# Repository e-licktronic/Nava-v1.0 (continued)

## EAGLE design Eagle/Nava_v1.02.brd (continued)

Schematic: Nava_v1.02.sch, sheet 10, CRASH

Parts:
C50: 100p; C050-025X075
C60, C86, C87, C127, C132: 10/16; E2-5
C126, C137: 0.001; C050-025X075
C131: 470p; C025_RE
C136: 0.0012; C050-025X075
C138: 0.0027; C050-025X075
C139: 390p; C025_RE
IC51, IC52, IC65: M5218; SIL8
IC58: 4520N; DIL16
IC59: 4011UB; DIL14
IC60: 4013N; DIL14
IC61: 4040N; DIL16
IC62: 27C256P; DIL28-6
IC63: 74HC174; DIL16
J3: 22-27-2041-04; 6410-04
Q70: 2SA798; SIP-5
Q71, Q75, Q76: 2SC2603; TO92-ECB
R189: 100K; 0207/7
R425: 47K; 0207/7
R426: 4.7K; 0207/7
R427, R430: 2.2K; 0207/7
R428: 220R; 0207/7
R429: 100R; 0207/7
R431: 22R; 0207/7
R432: 270K; 0207/7
R442, R458, R460: 10K; 0207/7
R443: 6.8K; 0207/7
R445: 22K; 0207/7
R456, R457, R459, R461: 5.6K; 0207/7
RA10A, RA11A: 5K; 0207/7
RA10B, RA11B: 10K; 0207/7
RA10C, RA11C: 20K; 0207/7
RA10D, RA11D: 40K; 0207/7
RA10E, RA11E: 80K; 0207/7
RA10F, RA11F: 160K; 0207/7
VR24: 50KB; EVUF
VR25: 10KB; EVUF

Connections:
+5V: C87.+, IC52.5 (+IN), IC59.14 (VDD), IC60.14 (VDD), IC61.16 (VDD), IC62.1 (VPP), IC62.28 (VCC), IC63.1 (RES), IC63.16 (VDD), R428.2, R429.2; also elsewhere on the board
+VRI: C60.+, IC65.8 (V+), Q75.C, Q76.C; also elsewhere on the board
-VRI: C86.-, IC65.4 (V-), R458.2, R460.2; also elsewhere on the board
ACCENT_CRASH: R426.1; also elsewhere on the board
CRASH_OUT: IC65.1 (OUT), J3.2, VR24.2 (S), VR24.3 (E)
GND: C60.-, C86.+, C87.-, C137.1, C139.- (2), IC51.5 (+IN), IC58.1 (CLK), IC59.7 (VSS), IC60.6 (S), IC60.7 (VSS), IC60.8 (S), IC61.8 (VSS), IC62.14 (GND), IC63.8 (VSS), IC65.3 (+IN), R189.2, R431.1, VR24.M1, VR25.M1; also elsewhere on the board
HT_OUT2: IC59.6 (I1), IC59.10 (O), IC60.11 (CLK), VR25.1 (A), VR25.2 (S)
unnamed: Q70.3 (E), R430.1
unnamed: R443.1, VR25.3 (E)
unnamed: IC59.8 (I0), IC59.9 (I1), R442.2
unnamed: C131.+ (1), R442.1, R443.2
unnamed: IC59.5 (I0), IC59.11 (O), R427.1
unnamed: C131.- (2), IC59.4 (O), IC60.3 (CLK)
unnamed: IC60.9 (D), IC60.12 (!Q)
unnamed: IC60.2 (!Q), IC60.5 (D), IC62.22 (!OE)
unnamed: IC59.1 (I0), IC60.13 (Q)
unnamed: IC59.3 (O), IC63.9 (CLK)
unnamed: IC59.2 (I1), IC60.1 (Q), IC61.10 (P1)
unnamed: IC62.19 (D7), IC63.3 (D0)
unnamed: IC62.18 (D6), IC63.4 (D1)
unnamed: IC62.17 (D5), IC63.6 (D2)
unnamed: IC62.16 (D4), IC63.11 (D3)
unnamed: IC62.15 (D3), IC63.13 (D4)
unnamed: IC62.13 (D2), IC63.14 (D5)
unnamed: C127.+, RA10A.2, RA10B.2, RA10C.2, RA10D.2, RA10E.2, RA10F.2
unnamed: R432.1, RA11A.2, RA11B.2, RA11C.2, RA11D.2, RA11E.2, RA11F.2
unnamed: C126.1, IC52.6 (-IN), Q70.2 (C1), R432.2
unnamed: C126.2, IC52.7 (OUT), R430.2
unnamed: Q70.5 (B2), R429.1
unnamed: C127.-, Q71.C, R431.2
unnamed: Q70.1 (B1), R426.2, R427.2, R428.1
unnamed: Q70.4 (C2), Q71.B
unnamed: C138.2, R459.1, R461.2
unnamed: C136.2, R456.1, R457.2
unnamed: C137.2, Q75.B, R457.1
unnamed: C139.+ (1), Q76.B, R461.1
unnamed: IC51.6 (-IN), Q71.E, R425.2
unnamed: IC51.7 (OUT), R425.1, R456.2
unnamed: C136.1, Q75.E, R458.1, R459.2
unnamed: C132.-, C138.1, Q76.E, R460.1
unnamed: IC65.2 (-IN), R445.1, VR24.1 (A)
unnamed: C132.+, R445.2
unnamed: IC58.2 (EN), IC61.1 (Q12), IC62.23 (A11), RA11D.1
unnamed: IC61.2 (Q6), IC62.5 (A5)
unnamed: IC61.3 (Q5), IC62.6 (A4)
unnamed: IC61.4 (Q7), IC62.4 (A6)
unnamed: IC61.5 (Q4), IC62.7 (A3)
unnamed: IC61.6 (Q3), IC62.8 (A2)
unnamed: IC61.7 (Q2), IC62.9 (A1)
unnamed: IC61.9 (Q1), IC62.10 (A0)
unnamed: IC61.12 (Q9), IC62.25 (A8)
unnamed: IC61.13 (Q8), IC62.3 (A7)
unnamed: IC61.14 (Q10), IC62.24 (A9), RA11F.1
unnamed: IC61.15 (Q11), IC62.21 (A10), RA11E.1
unnamed: IC58.3 (Q0), IC62.2 (A12), RA11C.1
unnamed: IC58.4 (Q1), IC62.26 (A13), RA11B.1
unnamed: IC58.5 (Q2), IC62.27 (A14), RA11A.1
unnamed: IC58.6 (Q3), IC59.12 (I0), IC59.13 (I1), IC62.20 (!CE)
unnamed: IC63.2 (Q0), RA10A.1
unnamed: IC63.5 (Q1), RA10B.1
unnamed: IC63.7 (Q2), RA10C.1
unnamed: IC63.10 (Q3), RA10D.1
unnamed: IC63.12 (Q4), RA10E.1
unnamed: C50.2, IC58.7 (RES), IC60.4 (R), IC60.10 (R), IC61.11 (RES), R189.1
unnamed: IC63.15 (Q5), RA10F.1
TRIG_CRASH: C50.1; also elsewhere on the board

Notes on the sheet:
Crash

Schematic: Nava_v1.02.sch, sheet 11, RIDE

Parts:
C123, C124, C128, C129, C133: 10/16; E2-5
C125, C145: 0.001; C050-025X075
C130: 470p; C025_RE
C140: 100p; C050-025X075
C144: 0.0012; C050-025X075
C146: 0.0027; C050-025X075
C147: 390p; C025_RE
IC51, IC52, IC64: M5218; SIL8
IC53: 74HC174; DIL16
IC54: 27C256P; DIL28-6
IC55: 4040N; DIL16
IC56: 4013N; DIL14
IC57: 4011UB; DIL14
IC58: 4520N; DIL16
J3: 22-27-2041-04; 6410-04
Q68: 2SA798; SIP-5
Q69, Q77, Q78: 2SC2603; TO92-ECB
R188: 100K; 0207/7
R424: 47K; 0207/7
R433: 220R; 0207/7
R434: 100R; 0207/7
R435: 4.7K; 0207/7
R436, R437: 2.2K; 0207/7
R438: 22R; 0207/7
R439: 470K; 0207/7
R440, R464, R466: 10K; 0207/7
R441: 6.8K; 0207/7
R446: 22K; 0207/7
R462, R463, R465, R467: 5.6K; 0207/7
RA12A, RA13A: 5K; 0207/7
RA12B, RA13B: 10K; 0207/7
RA12C, RA13C: 20K; 0207/7
RA12D, RA13D: 40K; 0207/7
RA12E, RA13E: 80K; 0207/7
RA12F, RA13F: 160K; 0207/7
RP7, RP8: 0; 0207/7
VR26: 50KB; EVUF
VR27: 10KB; EVUF

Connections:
+5V: C129.+, IC52.3 (+IN), IC53.1 (RES), IC53.16 (VDD), IC54.1 (VPP), IC54.28 (VCC), IC55.16 (VDD), IC56.14 (VDD), IC57.14 (VDD), IC58.16 (VDD), R433.2, R434.2; also elsewhere on the board
+15V: RP7.1; also elsewhere on the board
+VRI: C123.+, IC51.8 (V+), IC52.8 (V+), IC64.8 (V+), Q77.C, Q78.C, RP7.2; also elsewhere on the board
-15V: RP8.2; also elsewhere on the board
-VRI: C124.-, IC51.4 (V-), IC52.4 (V-), IC64.4 (V-), R464.2, R466.2, RP8.1; also elsewhere on the board
ACCENT_RIDE: R435.1; also elsewhere on the board
GND: C123.-, C124.+, C129.-, C145.1, C147.- (2), IC51.3 (+IN), IC53.8 (VSS), IC54.14 (GND), IC55.8 (VSS), IC56.6 (S), IC56.7 (VSS), IC56.8 (S), IC57.7 (VSS), IC58.8 (VSS), IC58.9 (CLK), IC64.3 (+IN), IC64.5 (+IN), R188.2, R438.1, VR26.M1, VR27.M1; also elsewhere on the board
HT_OUT1: IC56.11 (CLK), IC57.4 (O), IC57.8 (I0), VR27.1 (A), VR27.2 (S)
unnamed: Q68.3 (E), R436.1
unnamed: IC56.1 (Q), IC57.13 (I1), IC58.10 (EN)
unnamed: IC53.3 (D0), IC54.19 (D7)
unnamed: IC53.4 (D1), IC54.18 (D6)
unnamed: IC53.6 (D2), IC54.17 (D5)
unnamed: IC53.11 (D3), IC54.16 (D4)
unnamed: IC53.13 (D4), IC54.15 (D3)
unnamed: IC53.14 (D5), IC54.13 (D2)
unnamed: IC54.24 (A9), IC55.2 (Q6), RA13F.1
unnamed: IC54.25 (A8), IC55.3 (Q5)
unnamed: IC54.21 (A10), IC55.4 (Q7), RA13E.1
unnamed: IC54.3 (A7), IC55.5 (Q4)
unnamed: IC54.4 (A6), IC55.6 (Q3)
unnamed: IC54.5 (A5), IC55.7 (Q2)
unnamed: IC54.6 (A4), IC55.9 (Q1)
unnamed: IC54.2 (A12), IC55.12 (Q9), RA13C.1
unnamed: IC54.23 (A11), IC55.13 (Q8), RA13D.1
unnamed: IC54.26 (A13), IC55.14 (Q10), RA13B.1
unnamed: IC54.27 (A14), IC55.15 (Q11), RA13A.1
unnamed: IC54.10 (A0), IC58.11 (Q0)
unnamed: IC54.9 (A1), IC58.12 (Q1)
unnamed: IC57.5 (I0), IC57.6 (I1), R440.2
unnamed: IC54.8 (A2), IC58.13 (Q2)
unnamed: C130.+ (1), R440.1, R441.2
unnamed: IC57.3 (O), IC57.9 (I1), R437.1
unnamed: C130.- (2), IC56.3 (CLK), IC57.10 (O)
unnamed: IC54.20 (!CE), IC55.1 (Q12), IC57.1 (I0), IC57.2 (I1)
unnamed: IC53.2 (Q0), RA12A.1
unnamed: C146.2, R465.1, R467.2
unnamed: IC56.9 (D), IC56.12 (!Q)
unnamed: IC54.22 (!OE), IC56.2 (!Q), IC56.5 (D)
unnamed: IC56.13 (Q), IC57.12 (I0)
unnamed: IC53.5 (Q1), RA12B.1
unnamed: IC53.7 (Q2), RA12C.1
unnamed: IC53.9 (CLK), IC57.11 (O)
unnamed: IC53.10 (Q3), RA12D.1
unnamed: IC53.12 (Q4), RA12E.1
unnamed: IC53.15 (Q5), RA12F.1
unnamed: C128.+, RA12A.2, RA12B.2, RA12C.2, RA12D.2, RA12E.2, RA12F.2
unnamed: R439.1, RA13A.2, RA13B.2, RA13C.2, RA13D.2, RA13E.2, RA13F.2
unnamed: C125.1, IC52.2 (-IN), Q68.2 (C1), R439.2
unnamed: C125.2, IC52.1 (OUT), R436.2
unnamed: Q68.5 (B2), R434.1
unnamed: Q68.4 (C2), Q69.B
unnamed: C128.-, Q69.C, R438.2
unnamed: Q68.1 (B1), R433.1, R435.2, R437.2
unnamed: C144.2, R462.1, R463.2
unnamed: C145.2, Q77.B, R463.1
unnamed: C147.+ (1), Q78.B, R467.1
unnamed: IC51.2 (-IN), Q69.E, R424.2
unnamed: IC51.1 (OUT), R424.1, R462.2
unnamed: C144.1, Q77.E, R464.1, R465.2
unnamed: C133.+, R446.2
unnamed: C133.-, C146.1, Q78.E, R466.1
unnamed: IC64.2 (-IN), R446.1, VR26.1 (A)
unnamed: IC54.7 (A3), IC55.10 (P1), IC58.14 (Q3)
unnamed: C140.2, IC55.11 (RES), IC56.4 (R), IC56.10 (R), IC58.15 (RES), R188.1
unnamed: IC64.6 (-IN), IC64.7 (OUT)
unnamed: R441.1, VR27.3 (E)
RIDE_OUT: IC64.1 (OUT), J3.1, VR26.2 (S), VR26.3 (E)
TRIG_RIDE: C140.1; also elsewhere on the board

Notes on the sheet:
Ride

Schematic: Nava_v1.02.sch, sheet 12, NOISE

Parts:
C46: 4.7/50; E2-5
C47: 100p; C050-025X075
C48: 0.1; C050-024X044
C51, C52, C54, C161: 0.0047; C050-025X075
C53: 0.047; C050-025X075
D1, D2, D3, D26, D44, D45, D48, D49: 1N4148"; DO35-7C
IC27: M5218; SIL8
IC31: 4070N; DIL14
IC32, IC33: 4006N; DIL14
Q33, Q34: 2SC2603; TO92-ECB
R182, R183, R184, R191, R197: 10K; 0207/7
R185: 33K; 0207/7
R186, R194, R198, R200: 100K; 0207/7
R187: 47K; 0207/7
R190, R193, R196: 22K; 0207/7
R192: 220K; 0207/7
R195: 1K; 0207/7
R199: 47R; 0207/7
RP11, RP12: 0; 0207/7

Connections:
+15V: RP11.2; also elsewhere on the board
+VMT: C46.+, C48.1, IC27.8 (V+), IC31.2 (I1), IC31.14 (VDD), IC32.14 (VDD), IC33.14 (VDD), RP11.1; also elsewhere on the board
-15V: RP12.2; also elsewhere on the board
-VMT: IC27.4 (V-), RP12.1; also elsewhere on the board
GND: C48.2, C54.2, C161.2, D49.A, IC27.3 (+IN), IC31.6 (I1), IC31.7 (VSS), IC31.12 (I0), IC32.7 (VSS), IC33.7 (VSS), Q34.E, R182.1, R192.1, R197.2, R199.1; also elsewhere on the board
unnamed: C51.2, C161.1, R190.1
unnamed: C51.1, C52.2, R191.1
unnamed: C52.1, IC27.5 (+IN), R192.2
unnamed: C53.2, IC27.6 (-IN), IC27.7 (OUT), R191.2, R194.2
unnamed: C53.1, R195.1
unnamed: Q33.C, R195.2, R199.2
unnamed: IC27.2 (-IN), Q33.E, R193.2, R194.1
unnamed: Q33.B, R200.2
unnamed: Q34.B, R196.2, R197.1
unnamed: Q34.C, R198.2, R200.1
unnamed: IC32.4 (D2), IC32.13 (D1+4)
unnamed: D1.C, D2.C, D3.C, R196.1
unnamed: C54.1, D26.C, D44.C, D45.C, R198.1
unnamed: C46.-, D49.C, R182.2, R183.2
unnamed: IC31.13 (I1), R183.1, R186.2
unnamed: D48.A, IC31.11 (O), R186.1
unnamed: IC31.10 (O), R187.1
unnamed: IC33.4 (D2), IC33.13 (D1+4)
unnamed: IC31.9 (I1), IC32.6 (D4), IC32.10 (D3+4)
unnamed: IC32.5 (D3), IC32.12 (D2+5)
unnamed: D48.C, IC32.1 (D1), R187.2
unnamed: IC31.8 (I0), IC33.6 (D4), IC33.10 (D3+4)
unnamed: IC33.5 (D3), IC33.12 (D2+5)
unnamed: IC32.9 (D4+5), IC33.1 (D1)
unnamed: IC31.5 (I0), R185.2
unnamed: C47.1, R184.2, R185.1
unnamed: C47.2, IC31.1 (I0), IC31.4 (O)
unnamed: IC31.3 (O), IC32.3 (CLK), IC33.3 (CLK), R184.1
NOISE: IC33.9 (D4+5), R190.2; also elsewhere on the board
TOM_NOISE: IC27.1 (OUT), R193.1; also elsewhere on the board
TO_NOISE_HT: D26.A; also elsewhere on the board
TO_NOISE_LT: D45.A; also elsewhere on the board
TO_NOISE_MT: D44.A; also elsewhere on the board
TRIG_HT: D3.A; also elsewhere on the board
TRIG_LT: D1.A; also elsewhere on the board
TRIG_MT: D2.A; also elsewhere on the board

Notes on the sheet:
Noise

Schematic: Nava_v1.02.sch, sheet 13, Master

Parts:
C142, C152, C155: 10/16; E2-5
C143: 47/35; E2,5-6
C153, C154: 1/50; E2-5
D193, D194, D195: 1N4148"; DO35-7C
IC66: M5218; SIL8
J6: 22-27-2061-06; 6410-06
Q79: 2SA1115; TO92-ECB-PNP
Q82, Q83: 2SC2878; TO92-ECB
R468: 10K; 0207/7
R469, R470: 22K; 0207/7
R471: 4.7K; 0207/7
R472: 470K; 0207/7
R473, R474: 1K; 0207/7
RP19, RP20: 0; 0207/7
VR28: 50KB; PTV112-4

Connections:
+15V: RP19.1; also elsewhere on the board
+VMS: C143.+, D193.A, IC66.8 (V+), R468.1, RP19.2
-15V: RP20.1; also elsewhere on the board
-VMS: IC66.4 (V-), R471.2, R472.2, RP20.2
GND: C142.-, IC66.3 (+IN), IC66.5 (+IN), J6.2, J6.4, Q82.E, Q83.E; also elsewhere on the board
unnamed: D195.A, R471.1
unnamed: C143.-, D194.A, D195.C, R472.1
unnamed: IC66.7 (OUT), R474.1, VR28.1
unnamed: IC66.1 (OUT), R473.1, VR28.1' (1)
unnamed: D194.C, Q79.C, R469.1, R470.1
unnamed: C142.+, D193.C, Q79.E
unnamed: Q79.B, R468.2
unnamed: C154.-, IC66.2 (-IN), VR28.2' (2)
unnamed: C153.-, IC66.6 (-IN), VR28.2
unnamed: C155.-, R474.2
unnamed: C152.-, R473.2
unnamed: Q82.B, R469.2
unnamed: Q83.B, R470.2
unnamed: C153.+, J6.3
unnamed: C155.+, J6.5, Q83.C
unnamed: C152.+, J6.6, Q82.C
unnamed: C154.+, J6.1

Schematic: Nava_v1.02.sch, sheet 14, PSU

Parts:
C49, C88, C92, C93: 0.1; C050-024X044
C90, C91: 2200/35; E7,5-16
C94: 220/35; E3,5-8
C114, C141: 100/35; E3,5-8
C162: 680/35; E5-13
D94, D95, D96, D97, D109, D110, D111: 1N4004; DO41-7
D101: 1N5819-B; DO41-7.6
J8: KK-156-5
J9: KK-156-2
J16: JACK-PLUG0; JACK_PSU_2.1MM
L1: 33u; BS11
R40: 0; 0207/7
REG1: 7815TV; TO220V
REG2: MC79M15BT; TO220V
REG3: LM2596T; T05D

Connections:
+5V: C94.+, J8.2, L1.1, REG3.4 (FB); also elsewhere on the board
GND: C49.1, C88.2, C90.-, C91.+, C92.2, C93.1, C94.-, C114.-, C141.+, C162.-, D94.C, D95.A, D101.A, J8.3, J8.4, J16.1, R40.1, R40.2, REG1.2 (GND), REG2.1 (GND), REG3.3 (GND), REG3.5 (!ON!/OFF); also elsewhere on the board
unnamed: C49.2, C91.-, D96.A, D110.A, REG2.2 (VI)
unnamed: C88.1, C90.+, D97.C, D109.C, REG1.1 (VI)
unnamed: C92.1, C114.+, D95.C, D97.A, J8.1, REG1.3 (VO)
unnamed: D109.A, D110.C, D111.A, J9.2
unnamed: C93.2, C141.-, D94.A, D96.C, J8.5, REG2.3 (VO)
unnamed: C162.+, D111.C, REG3.1 (VIN)
unnamed: D101.C, L1.2, REG3.2 (OUT)
unnamed: J9.1, J16.3

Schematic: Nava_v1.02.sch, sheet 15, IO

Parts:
4, 5: LSP10
BASSDRUM: JACK_TRSNRJ6HF; JACK_TRS
C500, C502, C503, C504, C505, C506, C507, C508, C509, C510, C511, C512: 0.01; C050-025X075
CRASH: JACK_TRSNRJ6HF; JACK_TRS
D98: 1N4148"; DO35-7C
DIN_SYNC: MAB5SH
HANDCLAP: JACK_TRSNRJ6HF; JACK_TRS
HIHAT: JACK_TRSNRJ6HF; JACK_TRS
HITOM: JACK_TRSNRJ6HF; JACK_TRS
IC4: 6N138"; DIL08
IN: MAB5SH
J10: 22-27-2081-08; 6410-08
J11, J12, J13: 22-27-2041-04; 6410-04
J14: 22-27-2061-06; 6410-06
LEFT: JACK_TRSNRJ6HF; JACK_TRS
LOWTOM: JACK_TRSNRJ6HF; JACK_TRS
MIDTOM: JACK_TRSNRJ6HF; JACK_TRS
OUT: MAB5SH
Q66: 2N3906; TO92-EBC-SMALL
R314: 5.6K; 0207/7
R315, R316, R317, R318, R319: 220; 0207/7
R326, R327, R530, R532: 2.2K; 0207/7
R328, R330: 100K; 0207/7
R365: 1.2K; 0207/7
R500, R503, R506, R509, R512, R515, R518, R521, R524, R527, R552: 1K; 0207/7
R501, R502, R504, R505, R510, R511, R516, R517, R519, R520, R525: 12K; 0207/7
R507, R514, R523, R528: 8.2K; 0207/7
R508, R513, R522, R529: 15K; 0207/7
R526, R531, R533: 10K; 0207/7
R550: 47K; 0207/7
R551: 22K; 0207/7
RIDE: JACK_TRSNRJ6HF; JACK_TRS
RIGHT/MONO: JACK_TRSNRJ6HF; JACK_TRS
RIMSHOT: JACK_TRSNRJ6HF; JACK_TRS
SNAREDRUM: JACK_TRSNRJ6HF; JACK_TRS
THRU: MAB5SH
TRIG1: JACK_TRSNRJ6HF; JACK_TRS

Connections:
+5V: IC4.8 (VCC), J10.8, Q66.E, R315.2, R318.2, R365.1; also elsewhere on the board
DIN_CLK_IO: J10.4, R327.1, R330.1
DIN_START_IO: J10.5, R326.2, R328.1
GND: BASSDRUM.R, BASSDRUM.S, C500.1, C502.1, C503.1, C504.1, C505.1, C506.1, C507.1, C508.1, C509.1, C510.1, C511.1, C512.1, CRASH.R, CRASH.S, DIN_SYNC.2, DIN_SYNC.PE, DIN_SYNC.PE@ (PE), HANDCLAP.R, HANDCLAP.S, HIHAT.R, HIHAT.S, HITOM.R, HITOM.S, IC4.5 (GND), IN.PE, IN.PE@ (PE), J10.1, J10.2, J14.2, J14.4, LEFT.R, LEFT.S, LOWTOM.R, LOWTOM.S, MIDTOM.R, MIDTOM.S, OUT.2, OUT.PE, OUT.PE@ (PE), R314.1, R328.2, R330.2, R531.1, R533.1, R551.2, RIDE.R, RIDE.S, RIGHT/MONO.R, RIGHT/MONO.S, RIMSHOT.R, RIMSHOT.S, SNAREDRUM.R, SNAREDRUM.S, THRU.2, THRU.PE, THRU.PE@ (PE), TRIG1.R, TRIG1.S; also elsewhere on the board
MIDI_IN_IO: IC4.6 (VO), J10.7, R316.2, R365.2
MIDI_OUT_IO: J10.6, R319.2
unnamed: R552.1, TRIG1.T
unnamed: 5.MP, DIN_SYNC.5
unnamed: 4.MP, DIN_SYNC.4
unnamed: BASSDRUM.TN, R501.2, R502.2
unnamed: BASSDRUM.T, C500.2, R500.1
unnamed: Q66.B, R550.2
unnamed: J11.1, R500.2
unnamed: C512.2, LEFT.TN, R532.1, R533.2, RIGHT/MONO.T, RIGHT/MONO.TN
unnamed: R504.2, R505.2, SNAREDRUM.TN
unnamed: C502.2, R503.1, SNAREDRUM.T
unnamed: J11.2, R503.2
unnamed: C511.2, LEFT.T, R530.1, R531.2
unnamed: LOWTOM.TN, R507.2, R508.2
unnamed: C503.2, LOWTOM.T, R506.1
unnamed: J11.3, R506.2
unnamed: J12.1, R518.2
unnamed: MIDTOM.TN, R510.2, R511.2
unnamed: C504.2, MIDTOM.T, R509.1
unnamed: J12.2, R509.2
unnamed: J12.3, R515.2
unnamed: HITOM.TN, R513.2, R514.2
unnamed: C505.2, HITOM.T, R512.1
unnamed: J14.1, R502.1, R505.1, R508.1, R511.1, R514.1, R517.1, R520.1, R523.1, R526.1, R529.1
unnamed: J12.4, R512.2
unnamed: R516.2, R517.2, RIMSHOT.TN
unnamed: C506.2, R515.1, RIMSHOT.T
unnamed: J13.1, R527.2
unnamed: J13.2, R524.2
unnamed: HANDCLAP.TN, R519.2, R520.2
unnamed: IN.4, R317.1
unnamed: D98.C, IC4.2 (A), R317.2
unnamed: D98.A, IC4.3 (C), IN.5
unnamed: R315.1, THRU.4
unnamed: R316.1, THRU.5
unnamed: IC4.7 (VB), R314.2
unnamed: OUT.4, R318.1
unnamed: OUT.5, R319.1
unnamed: DIN_SYNC.1, R326.1
unnamed: DIN_SYNC.3, R327.2
unnamed: C507.2, HANDCLAP.T, R518.1
unnamed: Q66.C, R551.1, R552.2
unnamed: J13.3, R521.2
unnamed: HIHAT.TN, R522.2, R523.2
unnamed: C508.2, HIHAT.T, R521.1
unnamed: J14.5, R530.2
unnamed: J14.6, R532.2
unnamed: CRASH.TN, R525.2, R526.2
unnamed: C509.2, CRASH.T, R524.1
unnamed: R528.2, R529.2, RIDE.TN
unnamed: C510.2, R527.1, RIDE.T
unnamed: J14.3, R501.1, R504.1, R507.1, R510.1, R513.1, R516.1, R519.1, R522.1, R525.1, R528.1
TRIG_1_IO: J10.3, R550.1

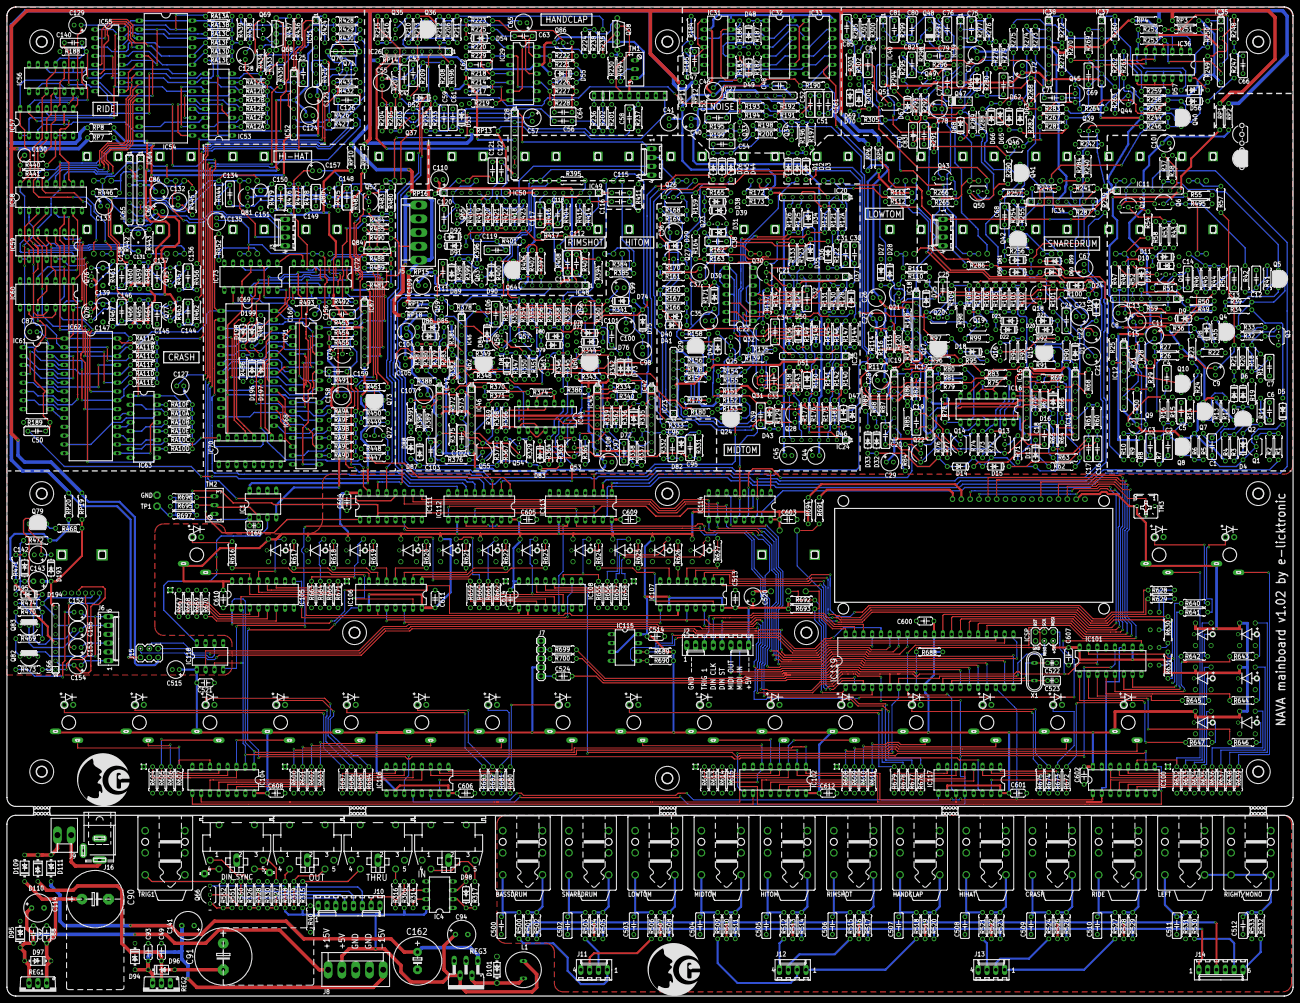
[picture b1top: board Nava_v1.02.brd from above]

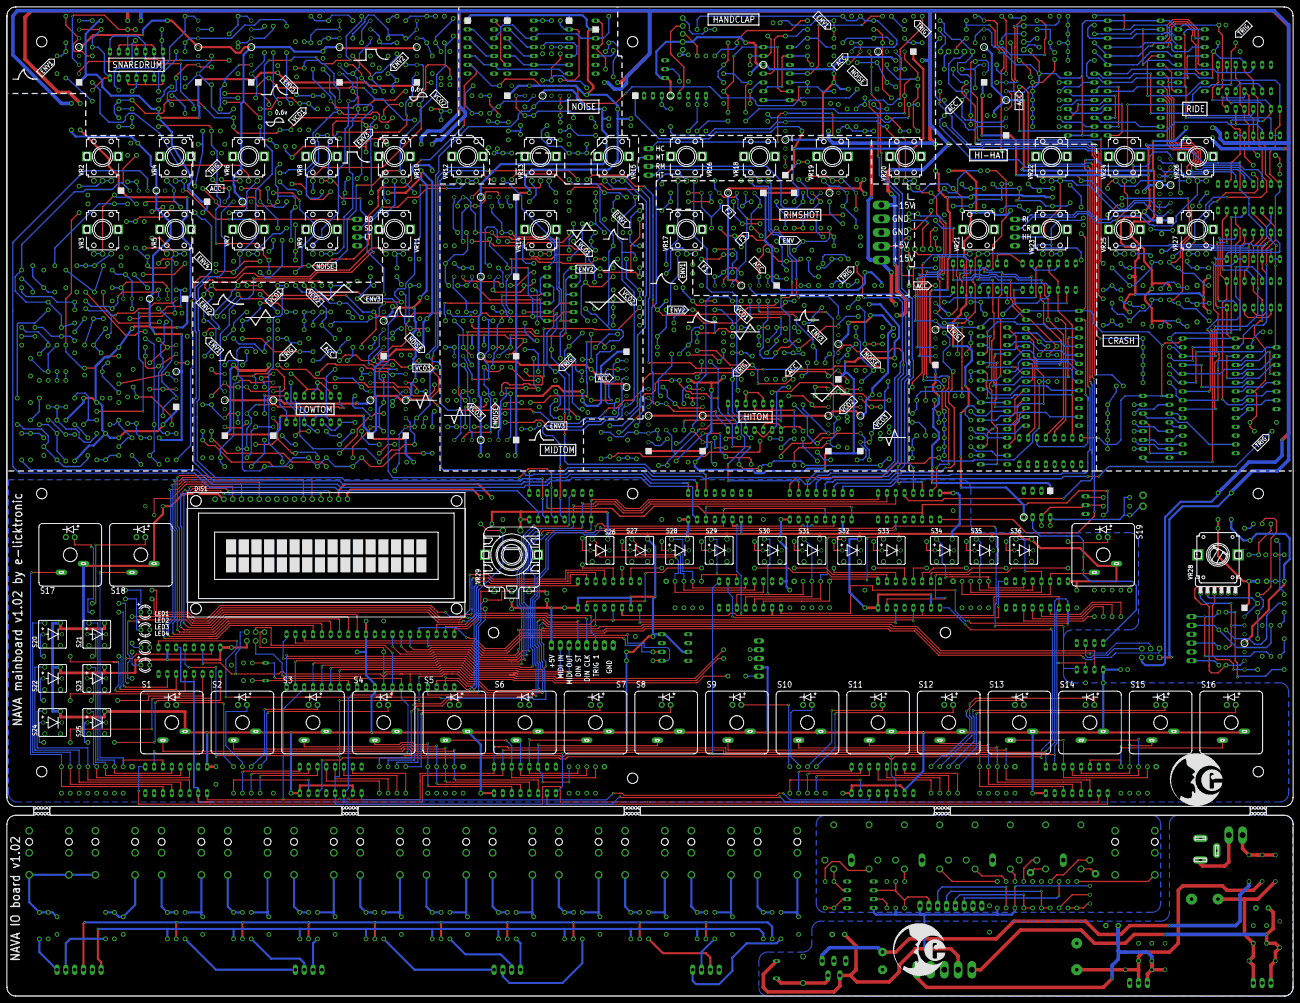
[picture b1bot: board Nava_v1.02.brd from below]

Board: 2 copper layers, 370.0 x 284.6 mm, 1261 parts (71 on the bottom side), 939 nets.

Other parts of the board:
U$1, U$13, U$14, U$15: LOGO_15MM_LITE
U$2, U$3, U$4, U$5, U$6, U$7, U$8, U$9, U$10, U$11, U$12: 3,0
U$16: TO92-EBC-NPN-SYM
U$17: TO92-EBC-PNP-SYM

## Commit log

2016-04-28 Create Read me
2016-04-28 Added files via upload
2016-04-28 Create keywords
2021-04-23 Initial Import
2021-04-23 Working on config page 2
2021-04-23 Implemented a separate MIDI channel for external instruments
2021-04-23 This commit gives a setting to allow pattern changes only at the end of a measure or free.
